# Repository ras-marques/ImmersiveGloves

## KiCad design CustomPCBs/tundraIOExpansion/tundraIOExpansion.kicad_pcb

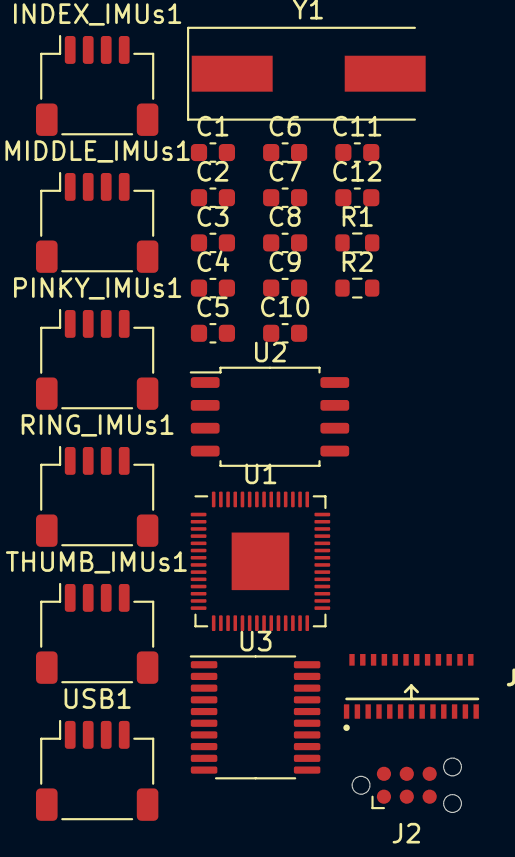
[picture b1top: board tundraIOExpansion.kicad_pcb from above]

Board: 2 copper layers, 26 parts (0 on the bottom side), 37 nets, no tracks yet.

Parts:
C1, C7, C10: 2.2u; C_0603_1608Metric
C2, C3, C4, C5, C6, C8, C9: 100n; C_0603_1608Metric
C11, C12: 20p; C_0603_1608Metric
INDEX_IMUs1: Conn_01x04; JST_SH_SM04B-SRSS-TB_1x04-1MP_P1.00mm_Horizontal
J1: Conn_01x25; 25PIN FRONT FLIP 0.6mm PITCH AYF332535A
J2: Conn_ARM_SWD_TagConnect_TC2030-NL; Tag-Connect_TC2030-IDC-NL_2x03_P1.27mm_Vertical
MIDDLE_IMUs1: Conn_01x04; JST_SH_SM04B-SRSS-TB_1x04-1MP_P1.00mm_Horizontal
PINKY_IMUs1: Conn_01x04; JST_SH_SM04B-SRSS-TB_1x04-1MP_P1.00mm_Horizontal
R1: 200; R_0603_1608Metric
R2: 1k; R_0603_1608Metric
RING_IMUs1: Conn_01x04; JST_SH_SM04B-SRSS-TB_1x04-1MP_P1.00mm_Horizontal
THUMB_IMUs1: Conn_01x04; JST_SH_SM04B-SRSS-TB_1x04-1MP_P1.00mm_Horizontal
U1: RP2040; QFN-56-1EP_7x7mm_P0.4mm_EP3.2x3.2mm
U2: MX25L3233FM2; SOP-8_5.28x5.23mm_P1.27mm
U3: TCA9544A; TSSOP-20_4.4x6.5mm_P0.65mm
USB1: Conn_01x04; JST_SH_SM04B-SRSS-TB_1x04-1MP_P1.00mm_Horizontal
Y1: Crystal; Crystal_SMD_HC49-SD

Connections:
+1V1: C7.1, C8.1, C9.1, U1.23 (DVDD), U1.45 (VREG_VOUT), U1.50 (DVDD)
+3V3: C1.1, C2.1, C3.1, C4.1, C5.1, C6.1, INDEX_IMUs1.1, J1.23, J2.1 (VCC), MIDDLE_IMUs1.4, PINKY_IMUs1.4, R1.1, RING_IMUs1.4, THUMB_IMUs1.4, U1.1 (IOVDD), U1.10 (IOVDD), U1.22 (IOVDD), U1.33 (IOVDD), U1.42 (IOVDD), U1.44 (VREG_IN), U1.48 (USB_VDD), U1.49 (IOVDD), U2.8 (VCC), U3.20 (VCC)
D10-MI_CS: J1.3, U1.16 (GPIO13)
D11-MI_MOSI: J1.5, U1.18 (GPIO15)
D12-MI_MISO: J1.4, U1.15 (GPIO12)
D13-MI_SCLK: J1.6, U1.17 (GPIO14)
GND: C1.2, C2.2, C3.2, C4.2, C5.2, C6.2, C7.2, C8.2, C9.2, C10.2, C11.2, C12.2, INDEX_IMUs1.4, J1.1, J1.2, J2.5 (GND), MIDDLE_IMUs1.1, PINKY_IMUs1.1, RING_IMUs1.1, THUMB_IMUs1.1, U1.19 (TESTEN), U1.57 (GND), U2.4 (GND), U3.10 (GND), USB1.1
unnamed: C12.1, R2.1, Y1.2
unnamed: INDEX_IMUs1.2, U1.5 (GPIO3)
unnamed: INDEX_IMUs1.3, U1.4 (GPIO2)
unnamed: J2.4 (SWCLK), U1.24 (SWCLK)
unnamed: J2.2 (SWDIO), U1.25 (SWD)
unnamed: J2.3 (~RESET), U1.26 (RUN)
unnamed: MIDDLE_IMUs1.2, U3.9 (SC1)
unnamed: MIDDLE_IMUs1.3, U3.8 (SD1)
unnamed: PINKY_IMUs1.2, U3.16 (SC3)
unnamed: PINKY_IMUs1.3, U3.15 (SD3)
unnamed: RING_IMUs1.2, U3.13 (SC2)
unnamed: RING_IMUs1.3, U3.12 (SD2)
unnamed: THUMB_IMUs1.2, U3.6 (SC0)
unnamed: THUMB_IMUs1.3, U3.5 (SD0)
unnamed: C10.1, R1.2, U1.43 (ADC_AVDD)
unnamed: U1.2 (GPIO0), U3.19 (SDA)
unnamed: U1.3 (GPIO1), U3.18 (SCL)
unnamed: U1.6 (GPIO4), U3.1 (A0)
unnamed: U1.7 (GPIO5), U3.2 (A1)
unnamed: U1.8 (GPIO6), U3.3 (A2)
unnamed: U1.52 (QSPI_SCLK), U2.6 (SCLK)
unnamed: U1.53 (QSPI_SD0), U2.5 (SI/SIO0)
unnamed: U1.55 (QSPI_SD1), U2.2 (SO/SIO1)
unnamed: U1.54 (QSPI_SD2), U2.3 (~WP/SIO2)
unnamed: U1.51 (QSPI_SD3), U2.7 (~HOLD/SIO3)
unnamed: U1.56 (QSPI_SS), U2.1 (~CS)
unnamed: U1.46 (USB_DM), USB1.2
unnamed: U1.47 (USB_DP), USB1.3
unnamed: C11.1, U1.20 (XIN), Y1.1
unnamed: R2.2, U1.21 (XOUT)

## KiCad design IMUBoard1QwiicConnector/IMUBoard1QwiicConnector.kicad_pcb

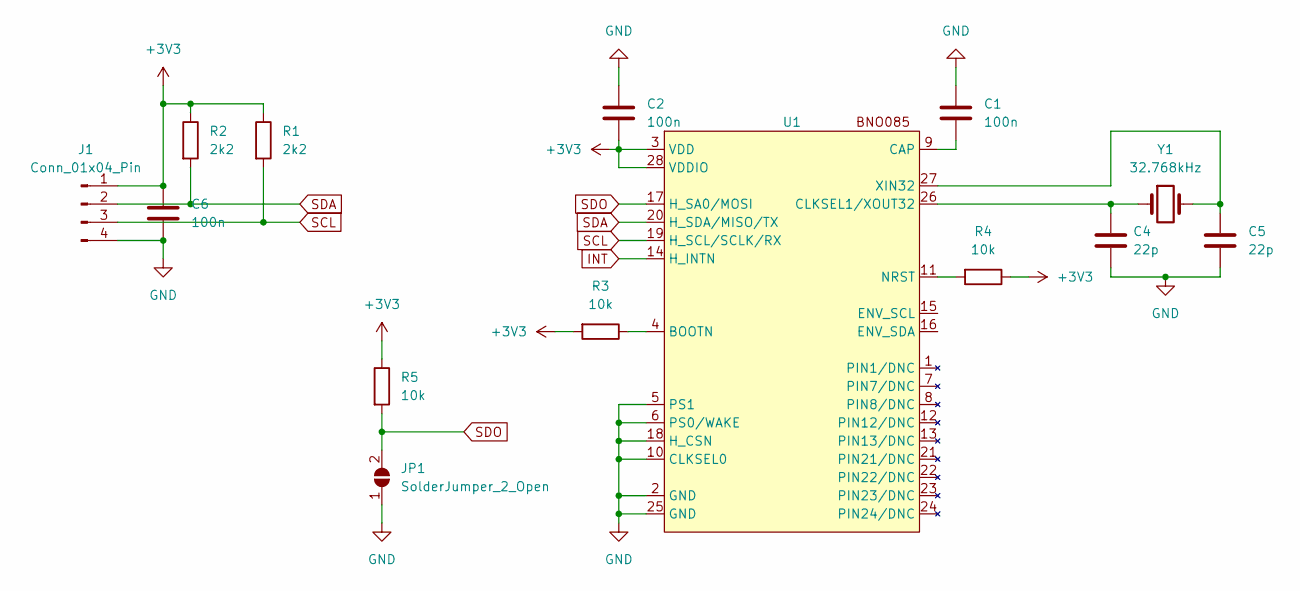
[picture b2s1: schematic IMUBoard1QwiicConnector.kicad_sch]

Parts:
C1, C2, C6: 100n; C_0603_1608Metric
C4, C5: 22p; C_0603_1608Metric
J1: Conn_01x04_Pin; JST_SH_SM04B-SRSS-TB_1x04-1MP_P1.00mm_Horizontal
JP1: SolderJumper_2_Open; SolderJumper-2_P1.3mm_Open_Pad1.0x1.5mm
R1, R2: 2k2; R_0603_1608Metric
R3, R4, R5: 10k; R_0603_1608Metric
U1: LGA-28_5.2x3.8mm_P0.5mm
Y1: 32.768kHz; Crystal_SMD_3215-2Pin_3.2x1.5mm

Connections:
+3V3: C2.2, C6.1, J1.1, R1.1, R2.1, R3.2, R4.1, R5.1, U1.3 (VDD), U1.28 (VDDIO)
GND: C1.1, C2.1, C4.2, C5.2, C6.2, J1.4, JP1.1 (A), U1.2 (GND), U1.5 (PS1), U1.6 (PS0/WAKE), U1.10 (CLKSEL0), U1.18 (H_CSN), U1.25 (GND)
INT: U1.14 (H_INTN)
unnamed: R3.1, U1.4 (BOOTN)
unnamed: C1.2, U1.9 (CAP)
unnamed: C4.1, U1.26 (CLKSEL1/XOUT32), Y1.1
unnamed: R4.2, U1.11 (NRST)
unnamed: C5.1, U1.27 (XIN32), Y1.2
SCL: J1.3, R1.2, U1.19 (H_SCL/SCLK/RX)
SDA: J1.2, R2.2, U1.20 (H_SDA/MISO/TX)
SDO: JP1.2 (B), R5.2, U1.17 (H_SA0/MOSI)

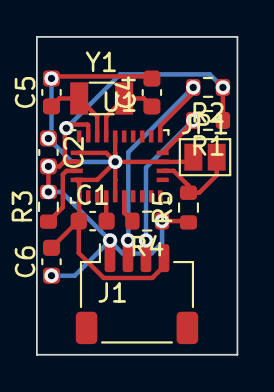
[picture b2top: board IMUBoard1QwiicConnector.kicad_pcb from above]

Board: 2 copper layers, 11.1 x 17.7 mm, 14 parts (0 on the bottom side), 10 nets.
